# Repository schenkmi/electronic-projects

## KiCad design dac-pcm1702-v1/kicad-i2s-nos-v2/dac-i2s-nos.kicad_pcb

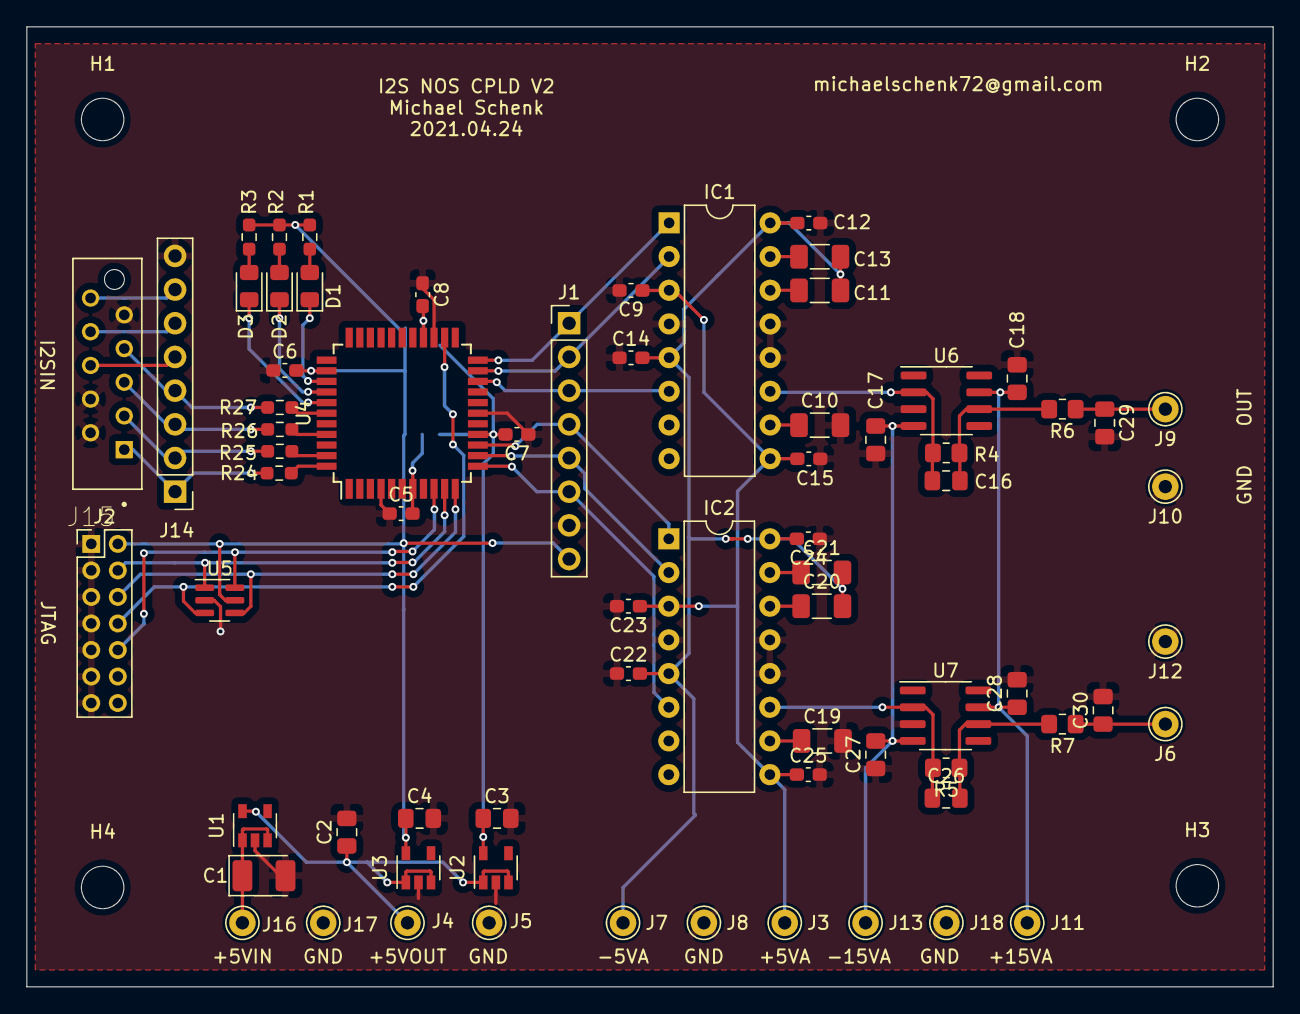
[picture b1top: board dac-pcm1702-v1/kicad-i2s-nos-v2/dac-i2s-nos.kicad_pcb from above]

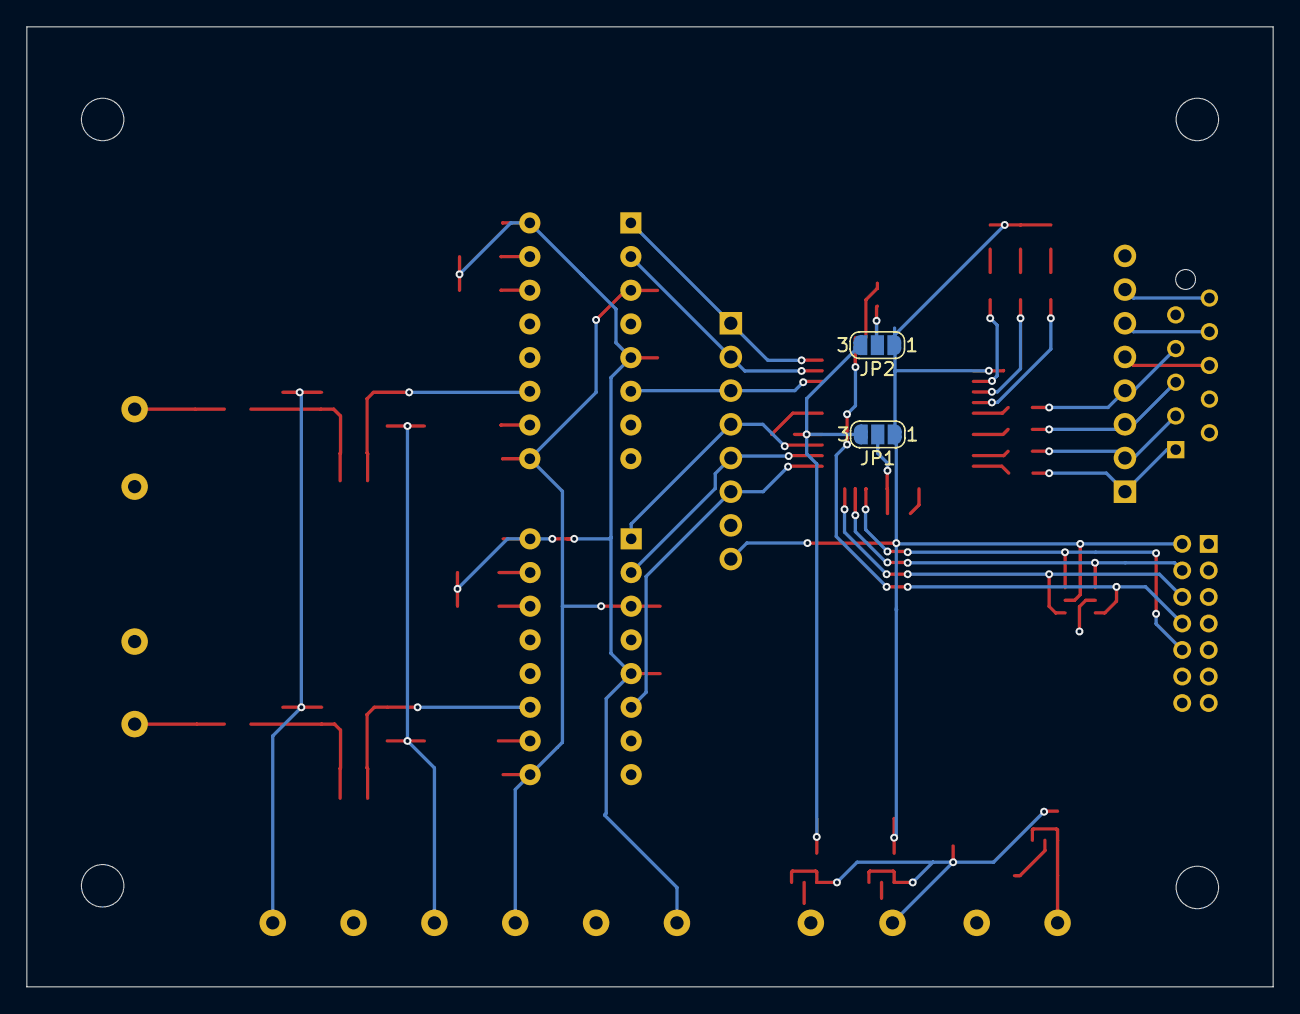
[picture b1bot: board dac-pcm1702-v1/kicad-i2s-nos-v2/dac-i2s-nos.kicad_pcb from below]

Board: 2 copper layers, 94.0 x 72.4 mm, 77 parts (2 on the bottom side), 50 nets.

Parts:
C1: 10uF; CP_EIA-3528-21_Kemet-B_Pad1.50x2.35mm_HandSolder
C2, C3, C4: 10uF; C_0805_2012Metric_Pad1.18x1.45mm_HandSolder
C5, C6, C7, C8: 100nF; C_0603_1608Metric_Pad1.08x0.95mm_HandSolder
C9, C13, C14, C15, C22, C23, C24, C25: 3.3uF; C_0603_1608Metric_Pad1.08x0.95mm_HandSolder
C10, C11, C12, C19, C20, C21: 100uF; C_1206_3216Metric_Pad1.33x1.80mm_HandSolder
C16, C26: 220pF; C_0805_2012Metric_Pad1.18x1.45mm_HandSolder
C17, C18, C27, C28: 1uF; C_0805_2012Metric_Pad1.18x1.45mm_HandSolder
C29, C30: 2n2; C_0805_2012Metric_Pad1.18x1.45mm_HandSolder
D1, D2, D3: LED; LED_0805_2012Metric_Pad1.15x1.40mm_HandSolder
H1, H2, H3, H4: MountingHole; MountingHole_3.2mm_M3
IC1, IC2: PCM1702P; DIP-16_W7.62mm
J1: Conn_01x08_Male; PinHeader_1x08_P2.54mm_Vertical
J2: Conn_02x07_Odd_Even; PinHeader_2x07_P2.00mm_Vertical
J3: +5VAIN; Pin_D1.0mm_L10.0mm
J4: +5VOUT; Pin_D1.0mm_L10.0mm
J5, J8, J10, J12, J17, J18: GND; Pin_D1.0mm_L10.0mm
J6, J9: OUT; Pin_D1.0mm_L10.0mm
J7: -5VAIN; Pin_D1.0mm_L10.0mm
J11: +15VAIN; Pin_D1.0mm_L10.0mm
J13: -15VAIN; Pin_D1.0mm_L10.0mm
J14: PORTA; PinHeader_1x08_P2.54mm_Vertical
J15: A; TE_CONN_RCPT_10POS_0.1_TIN_PCB
J16: +5VIN; Pin_D1.0mm_L10.0mm
JP1, JP2: SolderJumper_3_Open; SolderJumper-3_P1.3mm_Open_RoundedPad1.0x1.5mm_NumberLabels
R1, R2, R3: 330R; R_0603_1608Metric_Pad0.98x0.95mm_HandSolder
R4, R5, R7: 2.5k; R_0805_2012Metric_Pad1.20x1.40mm_HandSolder
R6: 470R; R_0805_2012Metric_Pad1.20x1.40mm_HandSolder
R24, R25, R26, R27: 33R; R_0603_1608Metric_Pad0.98x0.95mm_HandSolder
U1: TC1185-5.0VCT713; SOT-23-5
U2: TC1185-1.8VCT713; SOT-23-5
U3: TC1185-3.3VCT713; SOT-23-5
U4: XC2C64A-xVQ44; TQFP-44_10x10mm_P0.8mm
U5: CM1293A−04SO; SC-74-6_1.5x2.9mm_P0.95mm
U6, U7: OPA1641; SOIC-8_3.9x4.9mm_P1.27mm

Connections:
+1V8: C3.1, C7.2, JP1.3, JP2.3, U2.5, U4.15
+3V3: C4.1, C6.2, J1.8, J2.2, JP1.1, JP2.1, R1.1, R2.1, R3.1, U3.5, U4.35, U5.5
+5VA: C9.1, C15.1, C23.1, C25.1, IC1.3, IC1.9, IC2.3, IC2.9, J3.1
+15V: C18.1, C28.1, J11.1, U6.7, U7.7
-5VA: C11.2, C12.2, C13.2, C14.2, C20.2, C21.2, C22.2, C24.2, IC1.5, IC1.16, IC2.5, IC2.16, J7.1
-15V: C17.2, C27.2, J13.1, U6.4, U7.4
BCK: R25.2, U4.43
CLKOUTL: IC2.2, J1.5, U4.13
CLKOUTR: IC1.2, J1.2, U4.21
DATAIN: R27.2, U4.39
DATAOUTL: IC2.1, J1.4, U4.14
DATAOUTR: IC1.1, J1.1, U4.22
GND: C1.2, C2.2, C3.2, C4.2, C5.1, C6.1, C7.1, C8.1, C9.2, C10.2, C13.1, C14.1, C15.2, C17.1, C18.2, C19.2, C22.1, C23.2, C24.1, C25.2, C27.1, C28.2, C29.2, C30.2, IC1.4, IC1.12, IC1.13, IC2.4, IC2.12, IC2.13, J1.7, J2.1, J2.3, J2.5, J2.7, J2.9, J2.11, J2.13, J5.1, J8.1, J10.1, J12.1, J14.8, J15.2, J15.4, J15.9, J17.1, J18.1, U1.2, U2.2, U3.2, U4.4, U4.17, U4.25, U5.2, U6.3, U7.3
JTAG_TCK: J2.6, U4.11, U5.4
JTAG_TDI: J2.10, U4.9, U5.6
JTAG_TDO: J2.8, U4.24, U5.3
JTAG_TMS: J2.4, U4.10, U5.1
LEOUTL: IC2.6, J1.6, U4.12
LEOUTR: IC1.6, J1.3, U4.20
LRCK: R26.2, U4.41
MCLK: R24.2, U4.44
unnamed: C1.1, J16.1, U1.1, U1.3
unnamed: C2.1, J4.1, U1.5, U2.1, U2.3, U3.1, U3.3
unnamed: C5.2, JP1.2, U4.7
unnamed: C8.2, JP2.2, U4.26
unnamed: C10.1, IC1.10
unnamed: C11.1, IC1.14
unnamed: C12.1, IC1.15
unnamed: C16.1, IC1.11, R4.2, U6.2
unnamed: C16.2, R4.1, R6.2, U6.6
unnamed: C19.1, IC2.10
unnamed: C20.1, IC2.14
unnamed: C21.1, IC2.15
unnamed: C26.1, IC2.11, R5.2, U7.2
unnamed: C26.2, R5.1, R7.2, U7.6
unnamed: C29.1, J9.1, R6.1
unnamed: C30.1, J6.1, R7.1
unnamed: D1.1, U4.36
unnamed: D1.2, R1.2
unnamed: D2.1, U4.37
unnamed: D2.2, R2.2
unnamed: D3.1, U4.38
unnamed: D3.2, R3.2
unnamed: J14.1, J15.1, R24.1
unnamed: J14.2, J15.3, R25.1
unnamed: J14.3, J15.5, R26.1
unnamed: J14.4, J15.7, R27.1
unnamed: J14.5, J15.6
unnamed: J14.6, J15.8
unnamed: J14.7, J15.10

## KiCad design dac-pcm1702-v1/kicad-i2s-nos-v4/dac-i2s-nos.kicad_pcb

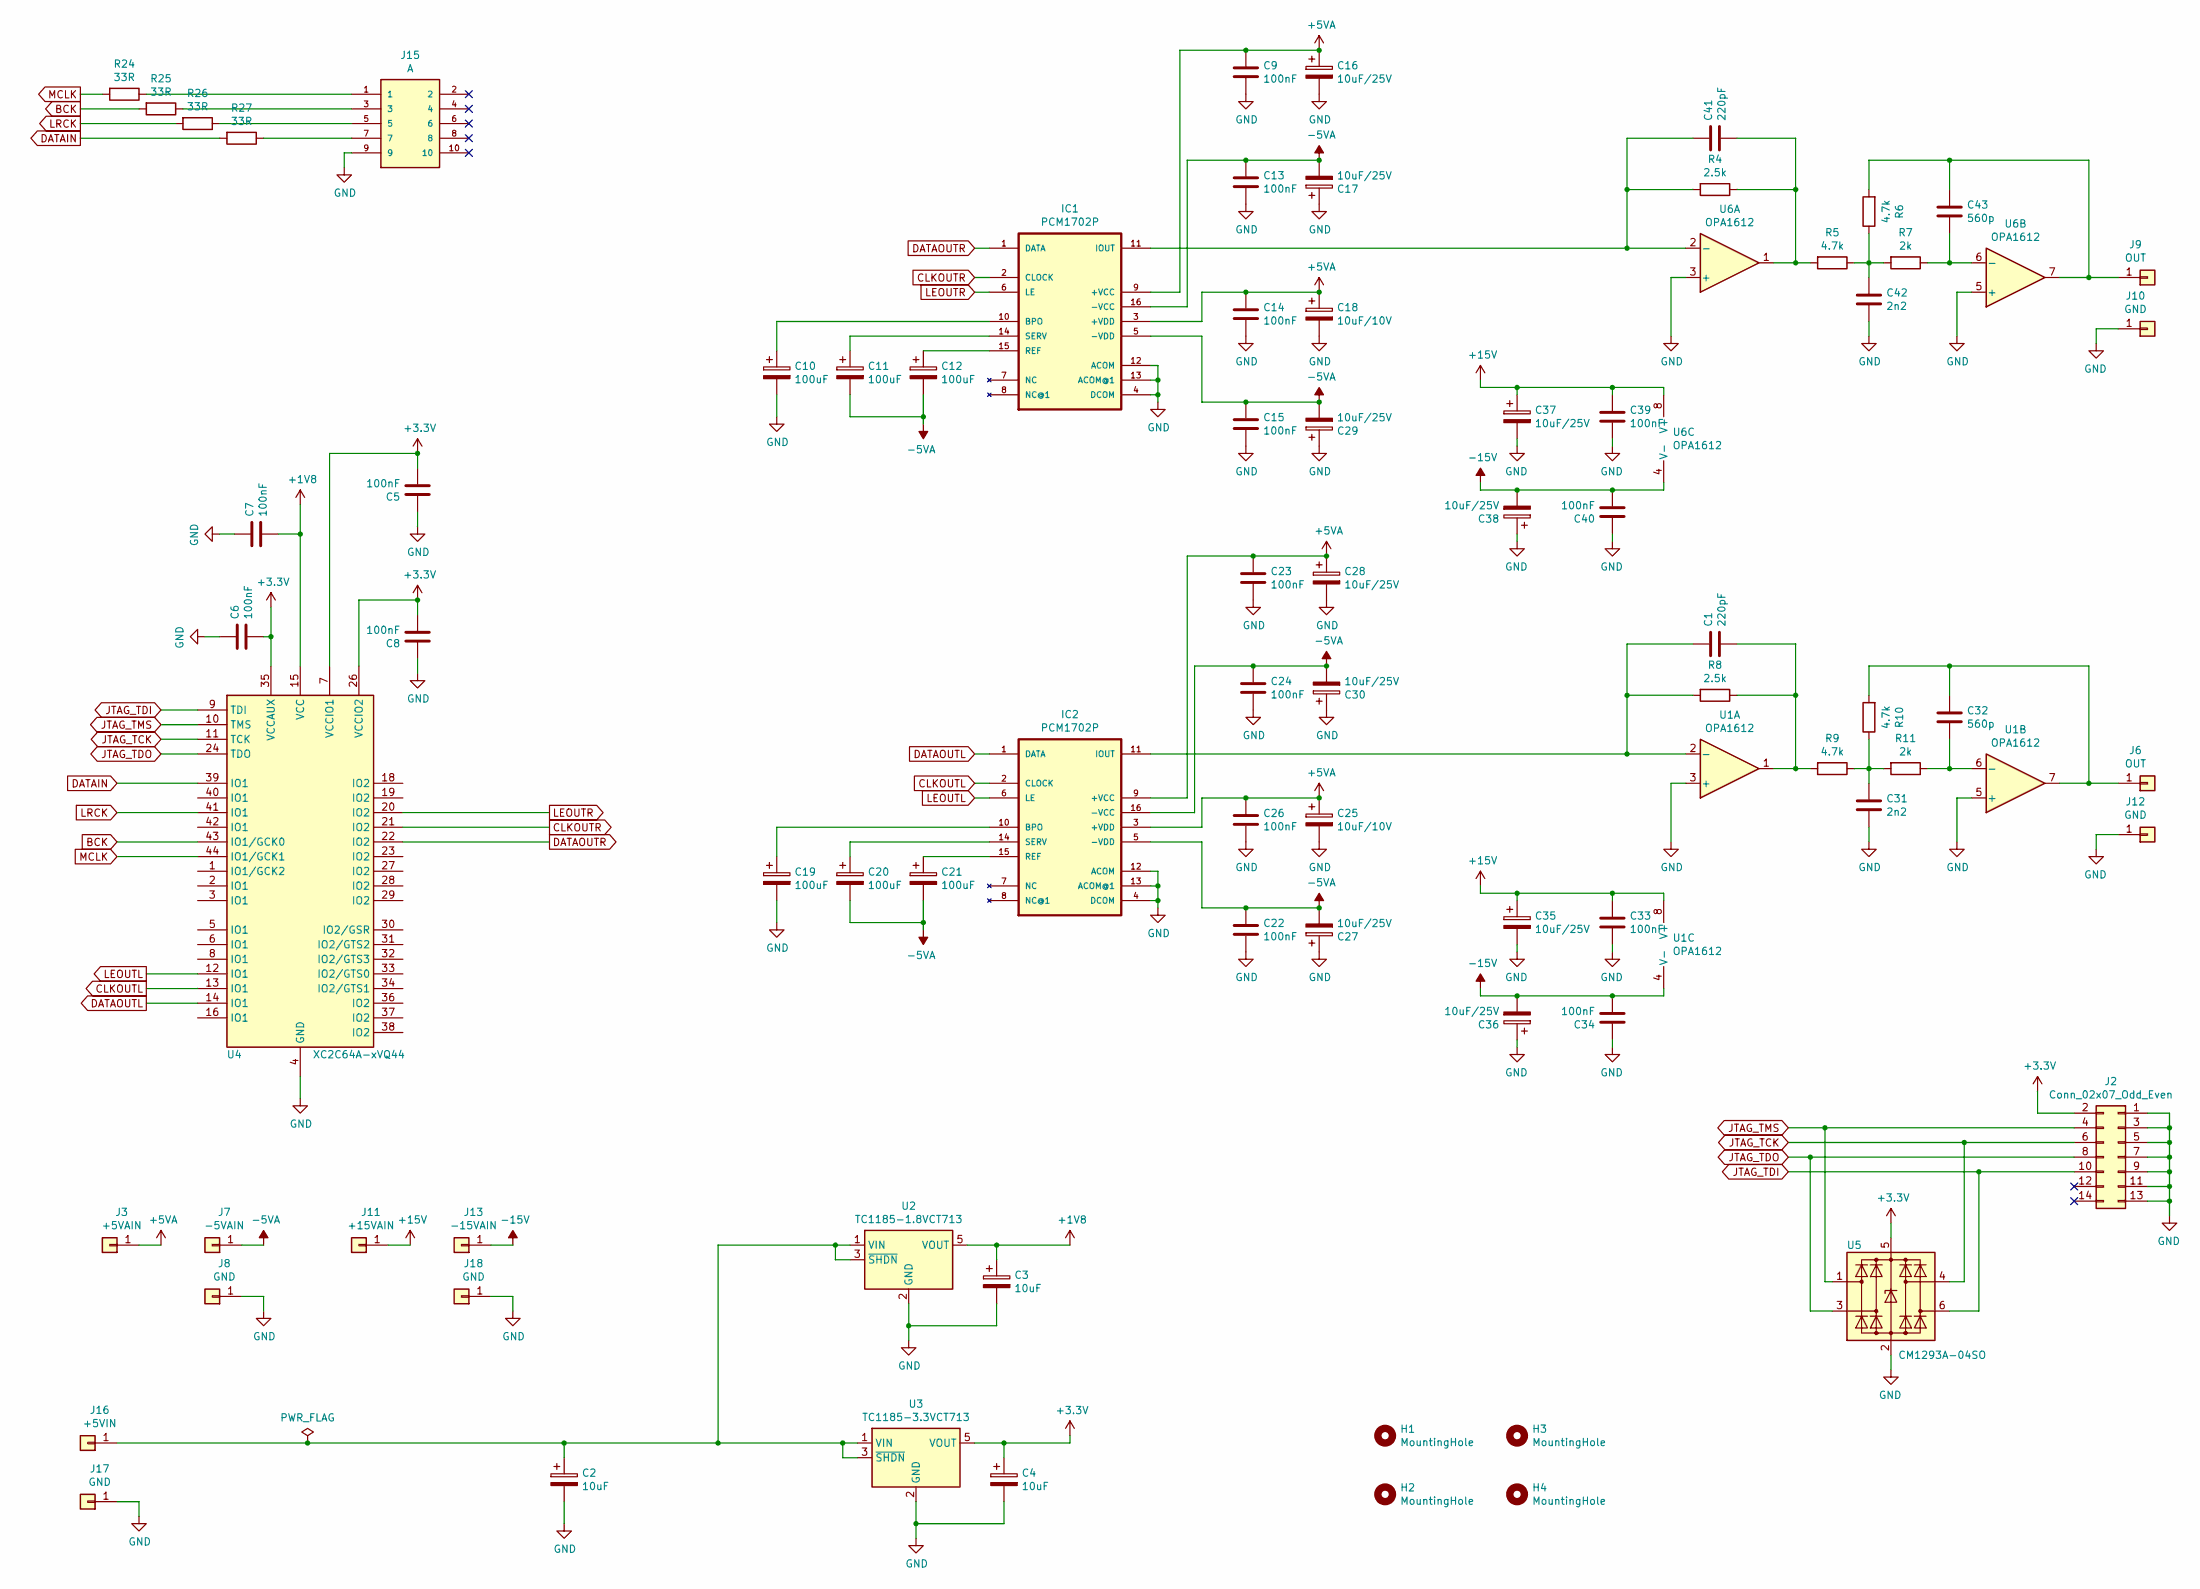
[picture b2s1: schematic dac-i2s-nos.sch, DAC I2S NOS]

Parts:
C1, C41: 220pF; C_0805_2012Metric_Pad1.18x1.45mm_HandSolder
C2, C3, C4: 10uF; C_0805_2012Metric_Pad1.18x1.45mm_HandSolder
C5, C6, C7, C8, C9, C13, C14, C15, C22, C23, C24, C26, C33, C34, C39, C40: 100nF; C_0603_1608Metric_Pad1.08x0.95mm_HandSolder
C10, C11, C12, C19, C20, C21: 100uF; C_1206_3216Metric_Pad1.33x1.80mm_HandSolder
C16, C17, C27, C28, C29, C30: 10uF/25V; CP_EIA-3216-18_Kemet-A_Pad1.58x1.35mm_HandSolder
C18, C25: 10uF/10V; CP_EIA-3216-18_Kemet-A_Pad1.58x1.35mm_HandSolder
C31, C42: 2n2; C_0805_2012Metric_Pad1.18x1.45mm_HandSolder
C32, C43: 560p; C_0805_2012Metric_Pad1.18x1.45mm_HandSolder
C35, C36, C37, C38: 10uF/25V; CP_EIA-3528-21_Kemet-B_Pad1.50x2.35mm_HandSolder
H1, H2, H3, H4: MountingHole; MountingHole_3.2mm_M3
IC1, IC2: PCM1702P; DIP-16_W7.62mm; MPN PCM1702P-J
J2: Conn_02x07_Odd_Even; PinHeader_2x07_P2.00mm_Vertical
J3: +5VAIN; Pin_D1.0mm_L10.0mm
J6, J9: OUT; Pin_D1.0mm_L10.0mm
J7: -5VAIN; Pin_D1.0mm_L10.0mm
J8, J10, J12, J17, J18: GND; Pin_D1.0mm_L10.0mm
J11: +15VAIN; Pin_D1.0mm_L10.0mm
J13: -15VAIN; Pin_D1.0mm_L10.0mm
J15: A; TE_CONN_RCPT_10POS_0.1_TIN_PCB
J16: +5VIN; Pin_D1.0mm_L10.0mm
R4, R8: 2.5k; R_0805_2012Metric_Pad1.20x1.40mm_HandSolder
R5, R6, R9, R10: 4.7k; R_0805_2012Metric_Pad1.20x1.40mm_HandSolder
R7, R11: 2k; R_0805_2012Metric_Pad1.20x1.40mm_HandSolder
R24, R25, R26, R27: 33R; R_0603_1608Metric_Pad0.98x0.95mm_HandSolder
U1, U6: OPA1612; SOIC-8_3.9x4.9mm_P1.27mm
U2: TC1185-1.8VCT713; SOT-23-5
U3: TC1185-3.3VCT713; SOT-23-5
U4: XC2C64A-xVQ44; TQFP-44_10x10mm_P0.8mm
U5: CM1293A−04SO; SC-74-6_1.5x2.9mm_P0.95mm

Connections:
+1V8: C3.1, C7.2, U2.5 (VOUT), U4.15 (VCC)
+3V3: C4.1, C5.2, C6.2, C8.2, J2.2, U3.5 (VOUT), U4.7 (VCCIO1), U4.26 (VCCIO2), U4.35 (VCCAUX), U5.5 (VBUS)
+5VA: C9.1, C14.1, C16.1, C18.1, C23.1, C25.1, C26.1, C28.1, IC1.3 (+VDD), IC1.9 (+VCC), IC2.3 (+VDD), IC2.9 (+VCC), J3.1
+15V: C33.1, C35.1, C37.1, C39.1, J11.1, U1.8 (V+), U6.8 (V+)
-5VA: C11.2, C12.2, C13.1, C15.1, C17.2, C20.2, C21.2, C22.1, C24.1, C27.2, C29.2, C30.2, IC1.5 (-VDD), IC1.16 (-VCC), IC2.5 (-VDD), IC2.16 (-VCC), J7.1
-15V: C34.2, C36.2, C38.2, C40.2, J13.1, U1.4 (V-), U6.4 (V-)
BCK: R25.2, U4.43 (IO1/GCK0)
CLKOUTL: IC2.2 (CLOCK), U4.13 (IO1)
CLKOUTR: IC1.2 (CLOCK), U4.21 (IO2)
DATAIN: R27.2, U4.39 (IO1)
DATAOUTL: IC2.1 (DATA), U4.14 (IO1)
DATAOUTR: IC1.1 (DATA), U4.22 (IO2)
GND: C2.2, C3.2, C4.2, C5.1, C6.1, C7.1, C8.1, C9.2, C10.2, C13.2, C14.2, C15.2, C16.2, C17.1, C18.2, C19.2, C22.2, C23.2, C24.2, C25.2, C26.2, C27.1, C28.2, C29.1, C30.1, C31.2, C33.2, C34.1, C35.2, C36.1, C37.2, C38.1, C39.2, C40.1, C42.2, IC1.4 (DCOM), IC1.12 (ACOM), IC1.13 (ACOM@1), IC2.4 (DCOM), IC2.12 (ACOM), IC2.13 (ACOM@1), J2.1, J2.3, J2.5, J2.7, J2.9, J2.11, J2.13, J8.1, J10.1, J12.1, J15.9, J17.1, J18.1, U1.3 (+), U1.5 (+), U2.2 (GND), U3.2 (GND), U4.4 (GND), U4.17 (GND), U4.25 (GND), U5.2 (GND), U6.3 (+), U6.5 (+)
JTAG_TCK: J2.6, U4.11 (TCK), U5.4 (I/O3)
JTAG_TDI: J2.10, U4.9 (TDI), U5.6 (I/O4)
JTAG_TDO: J2.8, U4.24 (TDO), U5.3 (I/O2)
JTAG_TMS: J2.4, U4.10 (TMS), U5.1 (I/O1)
LEOUTL: IC2.6 (LE), U4.12 (IO1)
LEOUTR: IC1.6 (LE), U4.20 (IO2)
LRCK: R26.2, U4.41 (IO1)
MCLK: R24.2, U4.44 (IO1/GCK1)
unnamed: C1.1, IC2.11 (IOUT), R8.2, U1.2 (-)
unnamed: C1.2, R8.1, R9.2, U1.1
unnamed: C2.1, J16.1, U2.1 (VIN), U2.3 (~SHDN), U3.1 (VIN), U3.3 (~SHDN)
unnamed: C10.1, IC1.10 (BPO)
unnamed: C11.1, IC1.14 (SERV)
unnamed: C12.1, IC1.15 (REF)
unnamed: C19.1, IC2.10 (BPO)
unnamed: C20.1, IC2.14 (SERV)
unnamed: C21.1, IC2.15 (REF)
unnamed: C31.1, R9.1, R10.1, R11.2
unnamed: C32.1, J6.1, R10.2, U1.7
unnamed: C32.2, R11.1, U1.6 (-)
unnamed: C41.1, IC1.11 (IOUT), R4.2, U6.2 (-)
unnamed: C41.2, R4.1, R5.2, U6.1
unnamed: C42.1, R5.1, R6.1, R7.2
unnamed: C43.1, J9.1, R6.2, U6.7
unnamed: C43.2, R7.1, U6.6 (-)
unnamed: J15.1, R24.1
unnamed: J15.3, R25.1
unnamed: J15.5, R26.1
unnamed: J15.7, R27.1

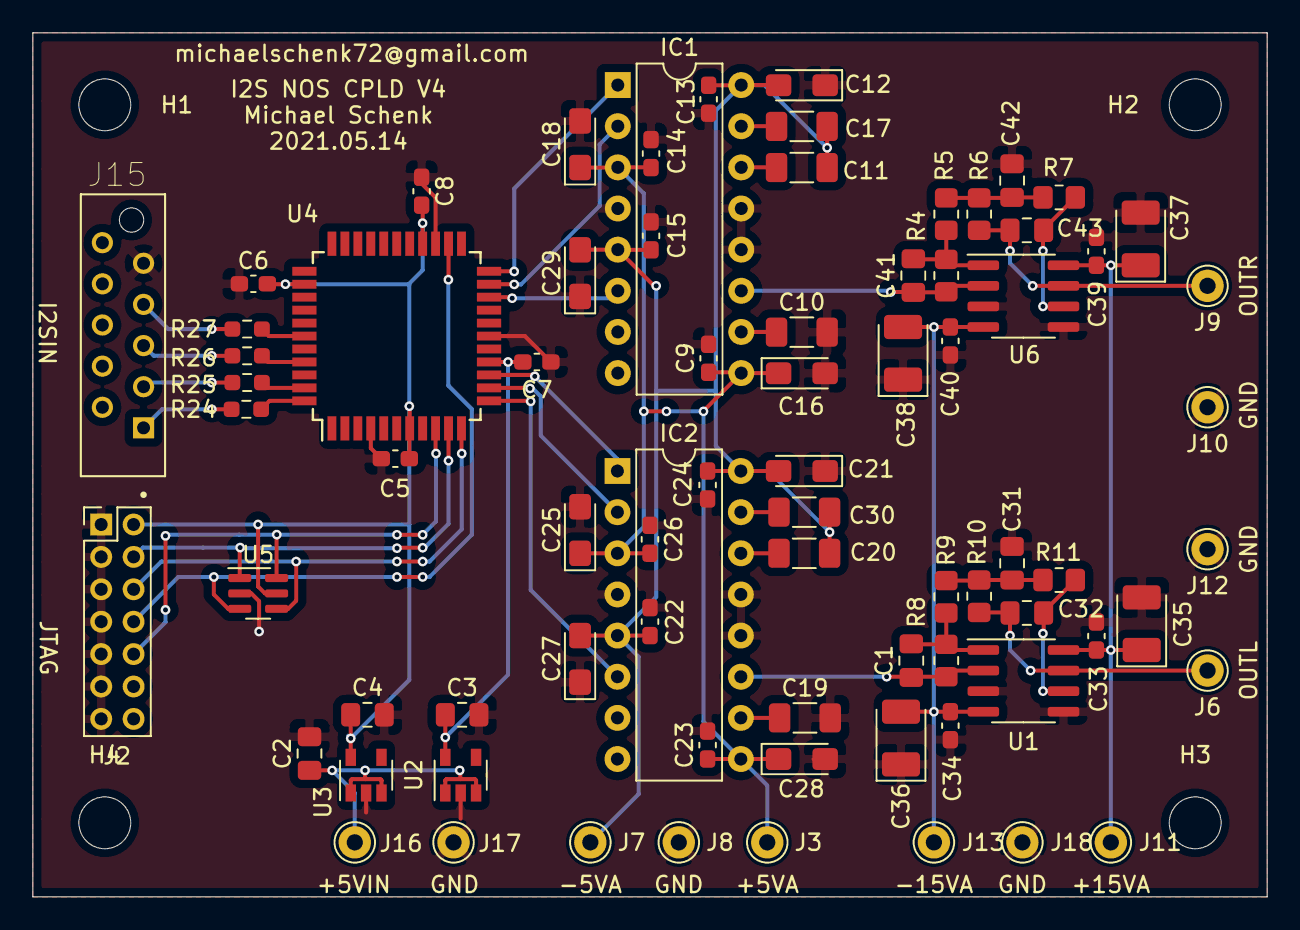
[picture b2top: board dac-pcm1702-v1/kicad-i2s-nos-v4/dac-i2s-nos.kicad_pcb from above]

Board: 2 copper layers, 76.2 x 53.3 mm, 81 parts (0 on the bottom side), 42 nets.

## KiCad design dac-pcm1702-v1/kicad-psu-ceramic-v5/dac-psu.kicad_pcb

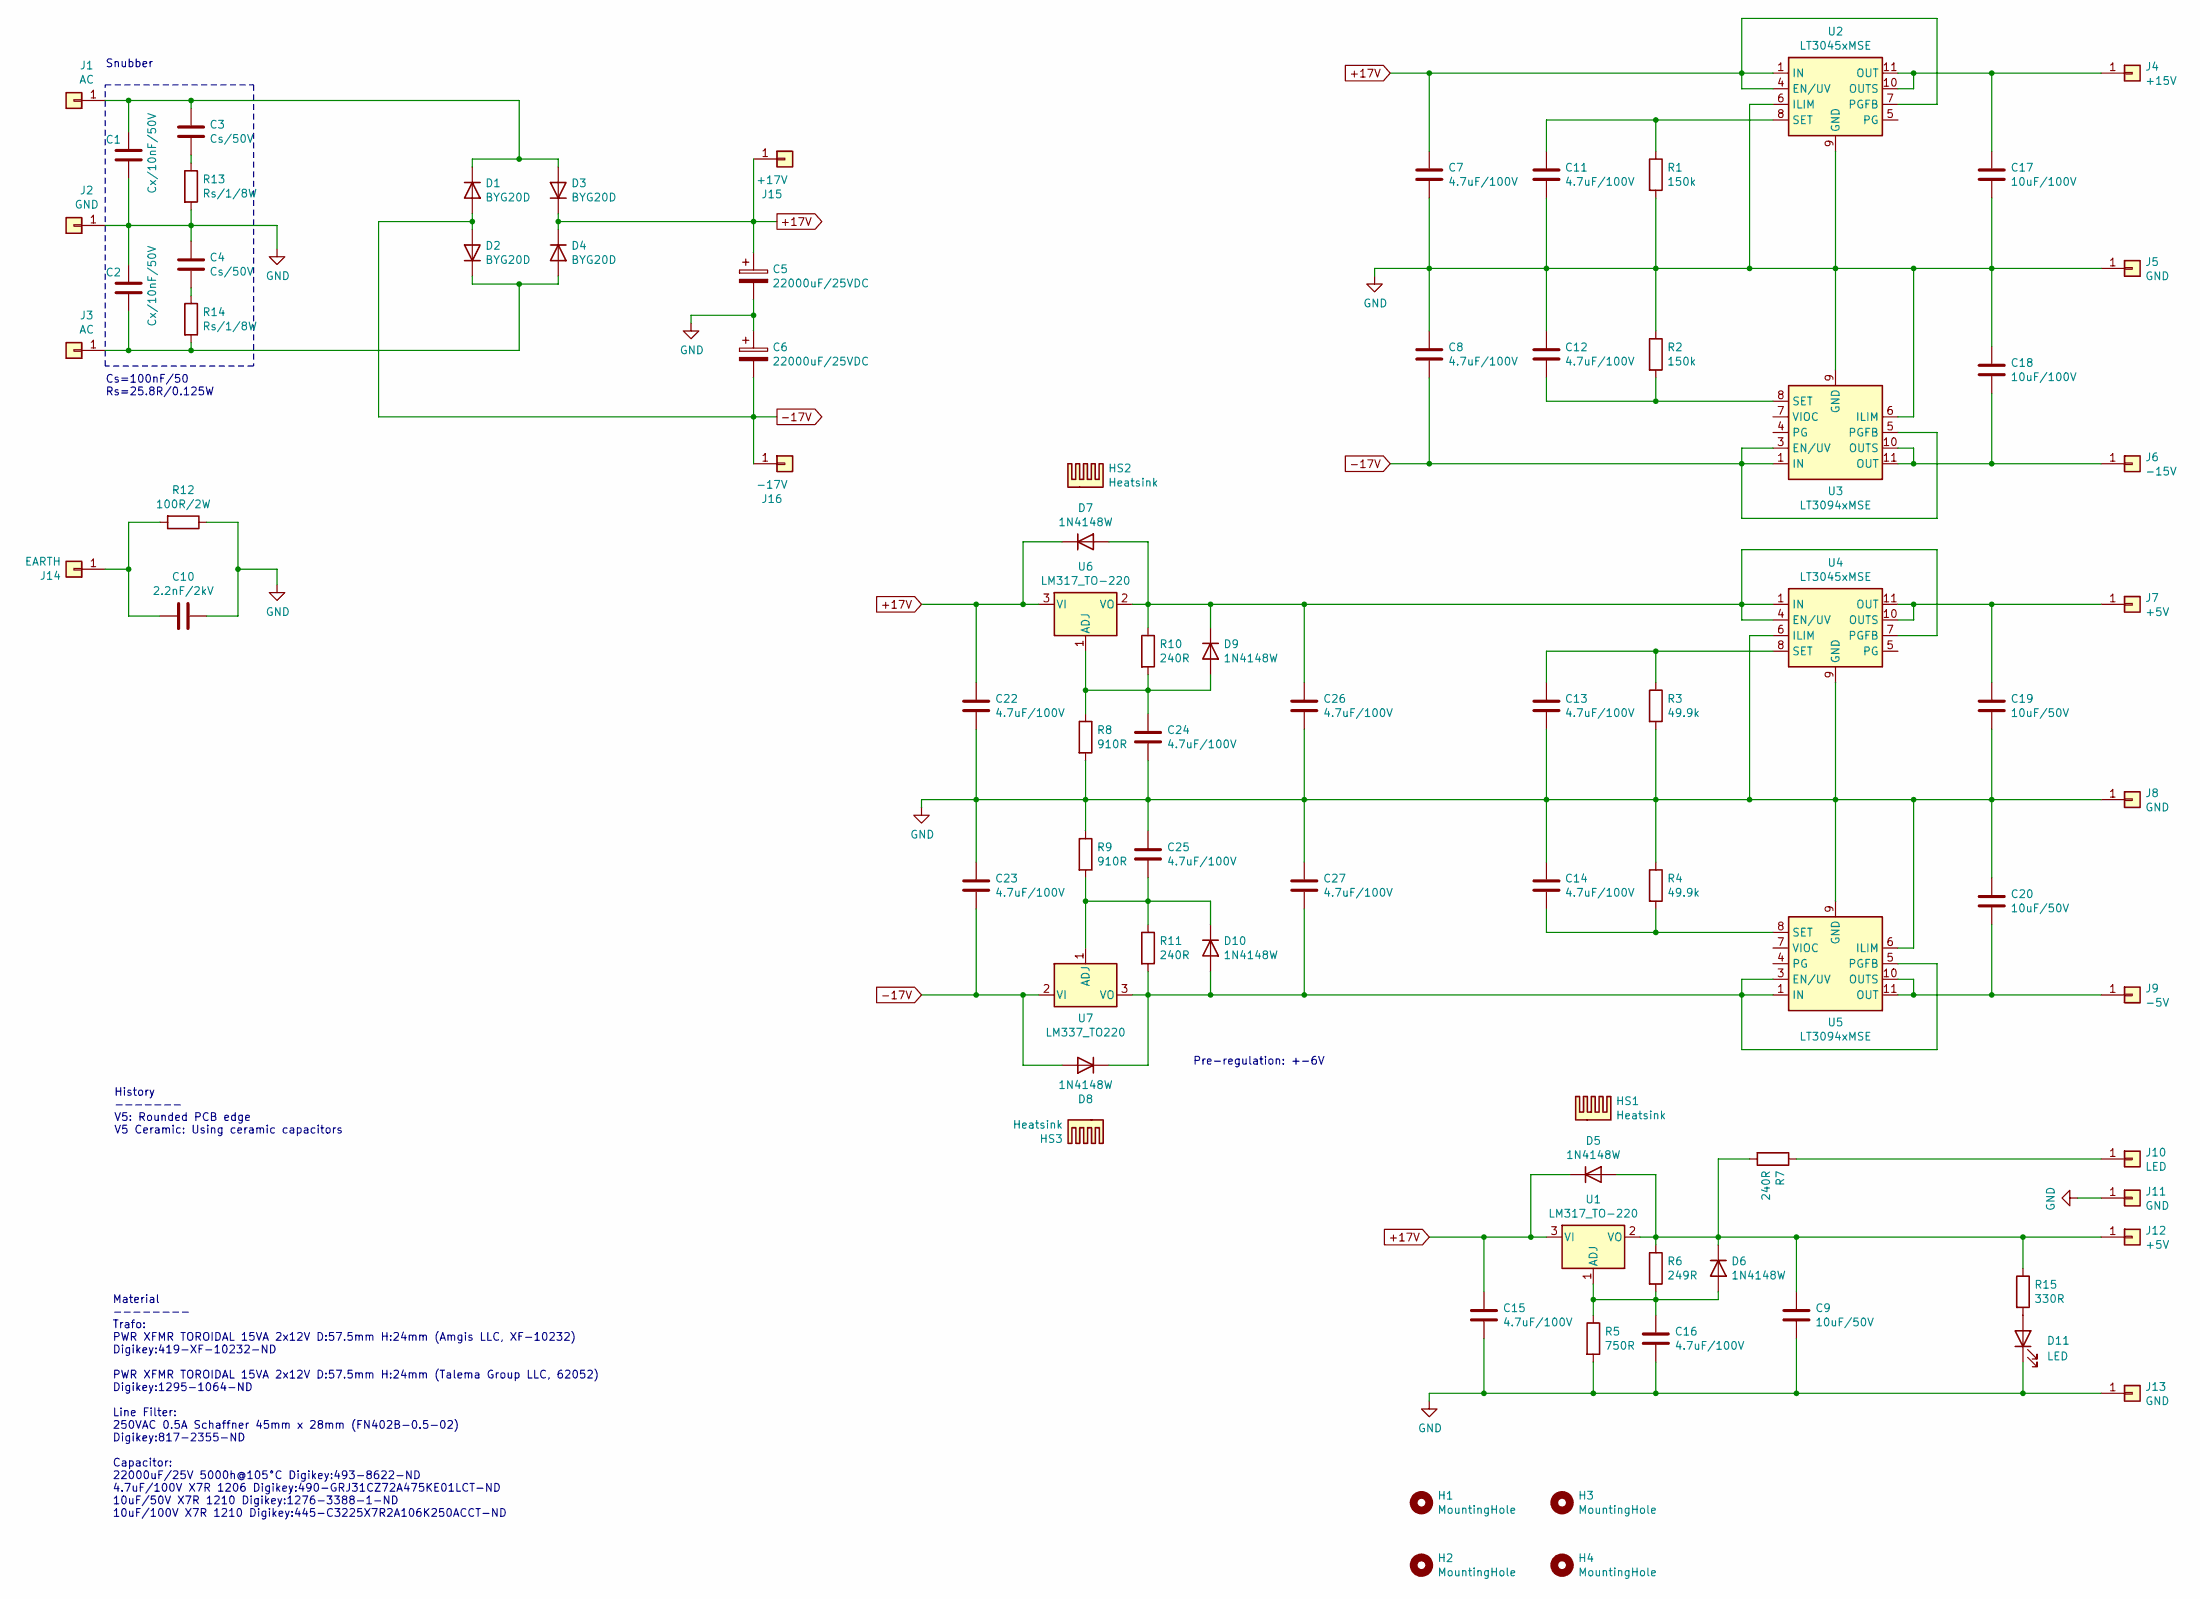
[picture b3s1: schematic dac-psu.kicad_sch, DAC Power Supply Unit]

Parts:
C1, C2: Cx/10nF/50V; C_0805_2012Metric_Pad1.18x1.45mm_HandSolder
C3, C4: Cs/50V; C_0805_2012Metric_Pad1.18x1.45mm_HandSolder
C5, C6: 22000uF/25VDC; CP_Radial_D35.0mm_P10.00mm_SnapIn
C7, C8, C11, C12, C13, C14, C15, C16, C22, C23, C24, C25, C26, C27: 4.7uF/100V; C_1206_3216Metric_Pad1.33x1.80mm_HandSolder
C9, C19, C20: 10uF/50V; C_1210_3225Metric_Pad1.33x2.70mm_HandSolder
C10: 2.2nF/2kV; C_Rect_L18.0mm_W5.0mm_P15.00mm_FKS3_FKP3
C17, C18: 10uF/100V; C_1210_3225Metric_Pad1.33x2.70mm_HandSolder
D1, D2, D3, D4: BYG20D; D_SMA_Handsoldering
D5, D6, D7, D8, D9, D10: 1N4148W; D_SOD-123
D11: LED; LED_0805_2012Metric_Pad1.15x1.40mm_HandSolder
H1, H2, H3, H4: MountingHole; MountingHole_3.2mm_M3_Pad_Via
HS1, HS2, HS3: Heatsink; Heatsink_Fischer_SK104-STC-STIC_35x13mm_2xDrill2.5mm
J1, J3: AC; Pin_D1.3mm_L11.0mm
J2: GND; Pin_D1.3mm_L11.0mm
J4: +15V; Pin_D1.0mm_L10.0mm
J5, J8, J11, J13: GND; Pin_D1.0mm_L10.0mm
J6: -15V; Pin_D1.0mm_L10.0mm
J7, J12: +5V; Pin_D1.0mm_L10.0mm
J9: -5V; Pin_D1.0mm_L10.0mm
J10: LED; Pin_D1.0mm_L10.0mm
J14: EARTH; Pin_D1.3mm_L11.0mm
J15: +17V; Pin_D1.3mm_L11.0mm
J16: -17V; Pin_D1.3mm_L11.0mm
R1, R2: 150k; R_0603_1608Metric_Pad0.98x0.95mm_HandSolder
R3, R4: 49.9k; R_0603_1608Metric_Pad0.98x0.95mm_HandSolder
R5: 750R; R_0603_1608Metric_Pad0.98x0.95mm_HandSolder
R6: 249R; R_0603_1608Metric_Pad0.98x0.95mm_HandSolder
R7, R10, R11: 240R; R_0603_1608Metric_Pad0.98x0.95mm_HandSolder
R8, R9: 910R; R_0603_1608Metric_Pad0.98x0.95mm_HandSolder
R12: 100R/2W; R_Axial_DIN0411_L9.9mm_D3.6mm_P15.24mm_Horizontal
R13, R14: Rs/1/8W; R_0805_2012Metric_Pad1.20x1.40mm_HandSolder
R15: 330R; R_0603_1608Metric_Pad0.98x0.95mm_HandSolder
U1, U6: LM317_TO-220; TO-220-3_Vertical
U2, U4: LT3045xMSE; MSOP-12-1EP_3x4.039mm_P0.65mm_EP1.651x2.845mm
U3, U5: LT3094xMSE; MSOP-12-1EP_3x4.039mm_P0.65mm_EP1.651x2.845mm
U7: LM337_TO220; TO-220-3_Vertical

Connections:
+17V: C5.1, C7.1, C15.1, C22.1, D3.1 (K), D4.1 (K), D5.1 (K), D7.1 (K), J15.1, U1.3 (VI), U2.1 (IN), U2.2 (IN), U2.3 (IN), U2.4 (EN/UV), U2.7 (PGFB), U6.3 (VI)
-17V: C6.2, C8.2, C23.2, D1.2 (A), D2.2 (A), D8.2 (A), J16.1, U3.1 (IN), U3.2 (IN), U3.3 (EN/UV), U3.5 (PGFB), U3.13 (IN), U7.2 (VI)
GND: C1.2, C2.1, C4.1, C5.2, C6.1, C7.2, C8.1, C9.2, C10.1, C11.2, C12.1, C13.2, C14.1, C15.2, C16.2, C17.2, C18.1, C19.2, C20.1, C22.2, C23.1, C24.2, C25.1, C26.2, C27.1, D11.1 (K), J2.1, J5.1, J8.1, J11.1, J13.1, R1.2, R2.1, R3.2, R4.1, R5.2, R8.2, R9.1, R12.1, R13.2, U2.6 (ILIM), U2.9 (GND), U2.13 (GND), U3.6 (ILIM), U3.9 (GND), U4.6 (ILIM), U4.9 (GND), U4.13 (GND), U5.6 (ILIM), U5.9 (GND)
unnamed: C3.2, R13.1
unnamed: C4.2, R14.1
unnamed: C1.1, C3.1, D1.1 (K), D3.2 (A), J1.1
unnamed: C2.2, D2.1 (K), D4.2 (A), J3.1, R14.2
unnamed: C9.1, D5.2 (A), D6.1 (K), J12.1, R6.1, R7.2, R15.1, U1.2 (VO)
unnamed: C16.1, D6.2 (A), R5.1, R6.2, U1.1 (ADJ)
unnamed: C26.1, D7.2 (A), D9.1 (K), R10.1, U4.1 (IN), U4.2 (IN), U4.3 (IN), U4.4 (EN/UV), U4.7 (PGFB), U6.2 (VO)
unnamed: C24.1, D9.2 (A), R8.1, R10.2, U6.1 (ADJ)
unnamed: C27.2, D8.1 (K), D10.2 (A), R11.2, U5.1 (IN), U5.2 (IN), U5.3 (EN/UV), U5.5 (PGFB), U5.13 (IN), U7.3 (VO)
unnamed: C25.2, D10.1 (K), R9.2, R11.1, U7.1 (ADJ)
unnamed: D11.2 (A), R15.2
unnamed: C17.1, J4.1, U2.10 (OUTS), U2.11 (OUT), U2.12 (OUT)
unnamed: C18.2, J6.1, U3.10 (OUTS), U3.11 (OUT), U3.12 (OUT)
unnamed: C19.1, J7.1, U4.10 (OUTS), U4.11 (OUT), U4.12 (OUT)
unnamed: C20.2, J9.1, U5.10 (OUTS), U5.11 (OUT), U5.12 (OUT)
unnamed: J10.1, R7.1
unnamed: C10.2, J14.1, R12.2
unnamed: C11.1, R1.1, U2.8 (SET)
unnamed: C12.2, R2.2, U3.8 (SET)
unnamed: C13.1, R3.1, U4.8 (SET)
unnamed: C14.2, R4.2, U5.8 (SET)

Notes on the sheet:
Material -------- Trafo: PWR XFMR TOROIDAL 15VA 2x12V D:57.5mm H:24mm (Amgis LLC, XF-10232) Digikey:419-XF-10232-ND PWR XFMR TOROIDAL 15VA 2x12V D:57.5mm H:24mm (Talema Group LLC, 62052) Digikey:1295-1064-ND Line Filter: 250VAC 0.5A Schaffner 45mm x 28mm (FN402B-0.5-02) Digikey:817-2355-ND Capacito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
Snubber
Cs=100nF/50 Rs=25.8R/0.125W
Pre-regulation: +-6V
History ------- V5: Rounded PCB edge V5 Ceramic: Using ceramic capacitors

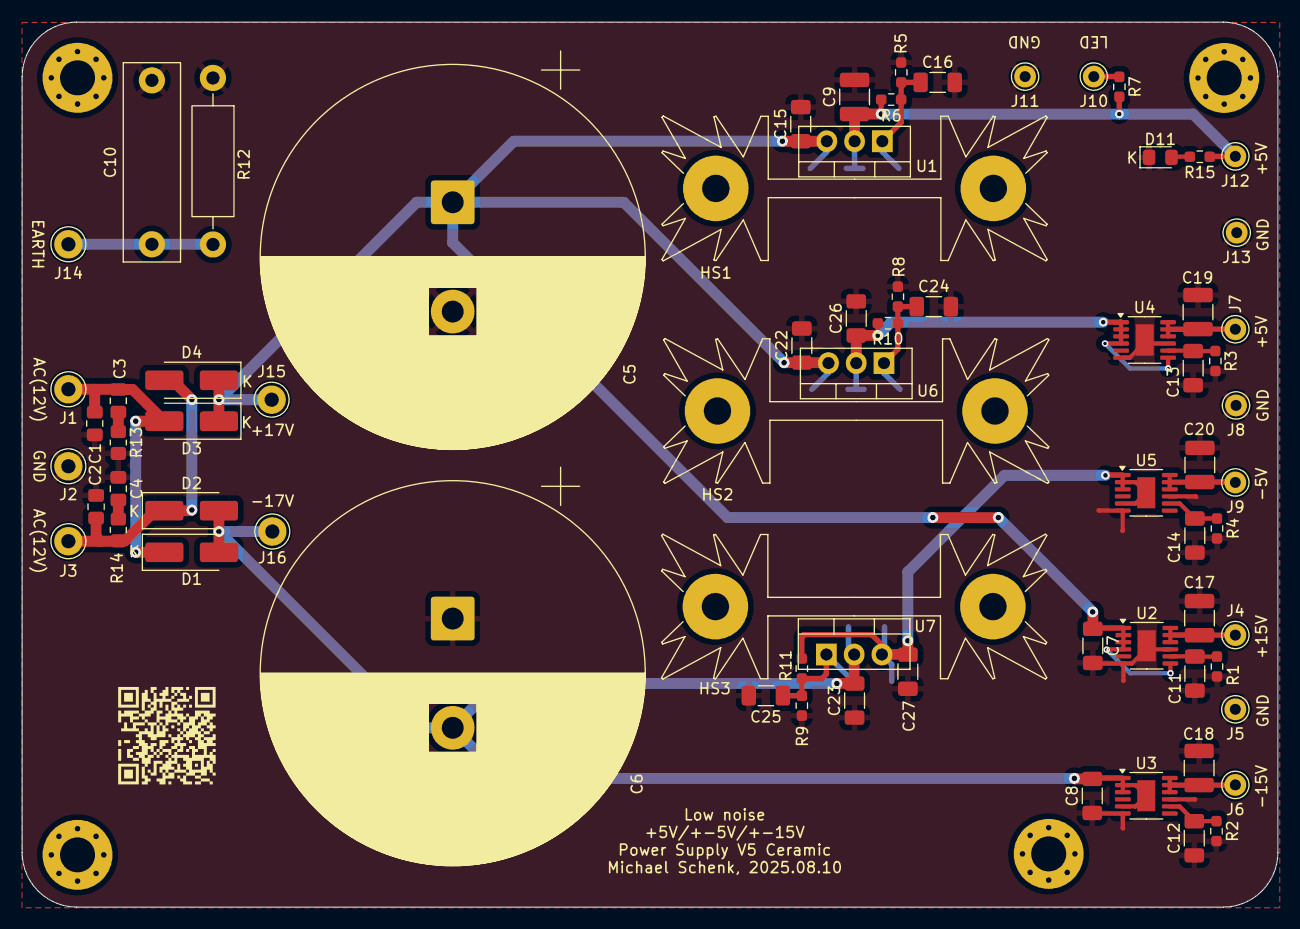
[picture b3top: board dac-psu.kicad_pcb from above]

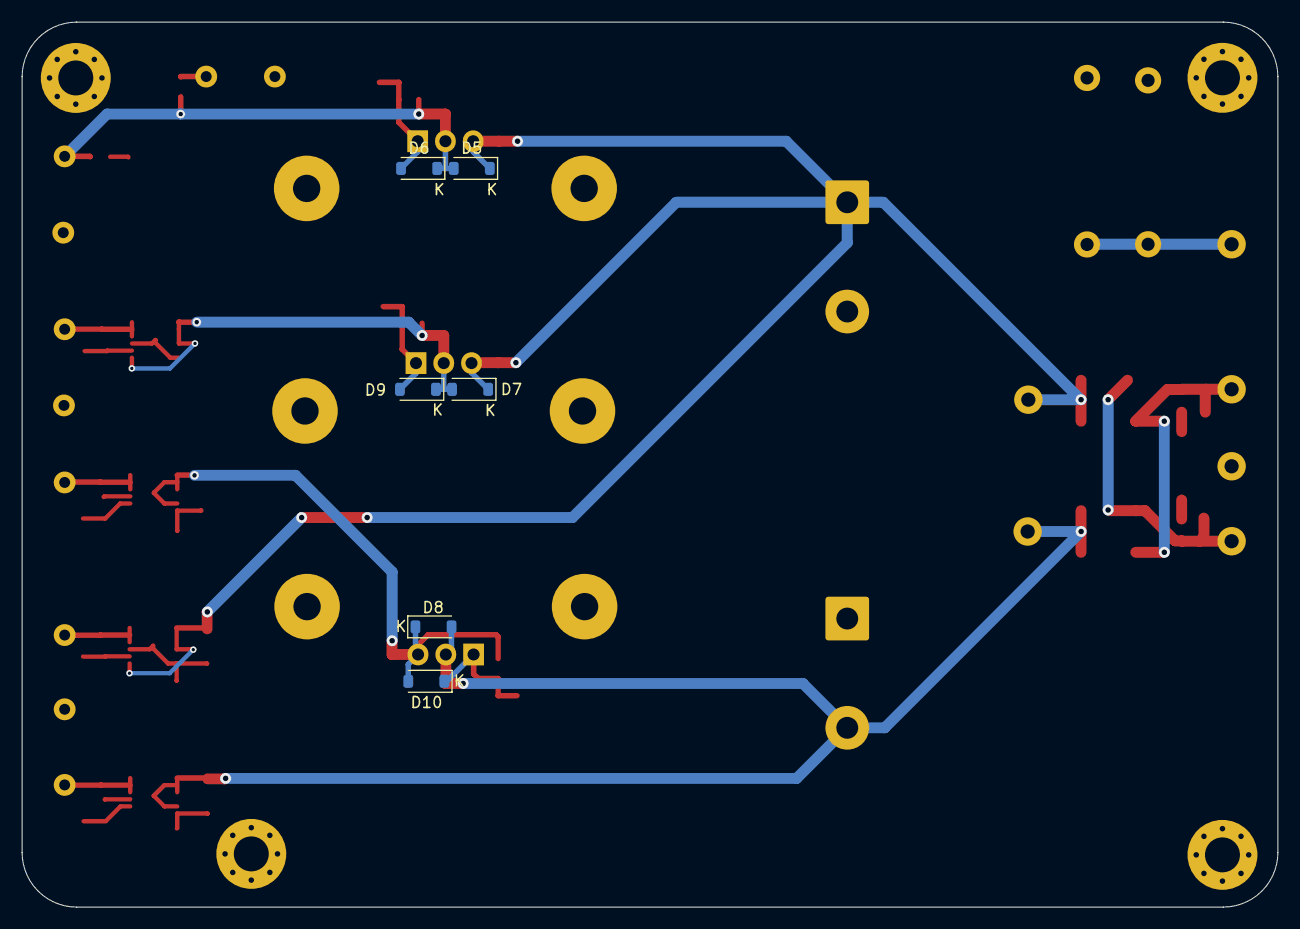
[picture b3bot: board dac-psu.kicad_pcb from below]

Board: 2 copper layers, 114.9 x 81.0 mm, 82 parts (6 on the bottom side), 24 nets.
